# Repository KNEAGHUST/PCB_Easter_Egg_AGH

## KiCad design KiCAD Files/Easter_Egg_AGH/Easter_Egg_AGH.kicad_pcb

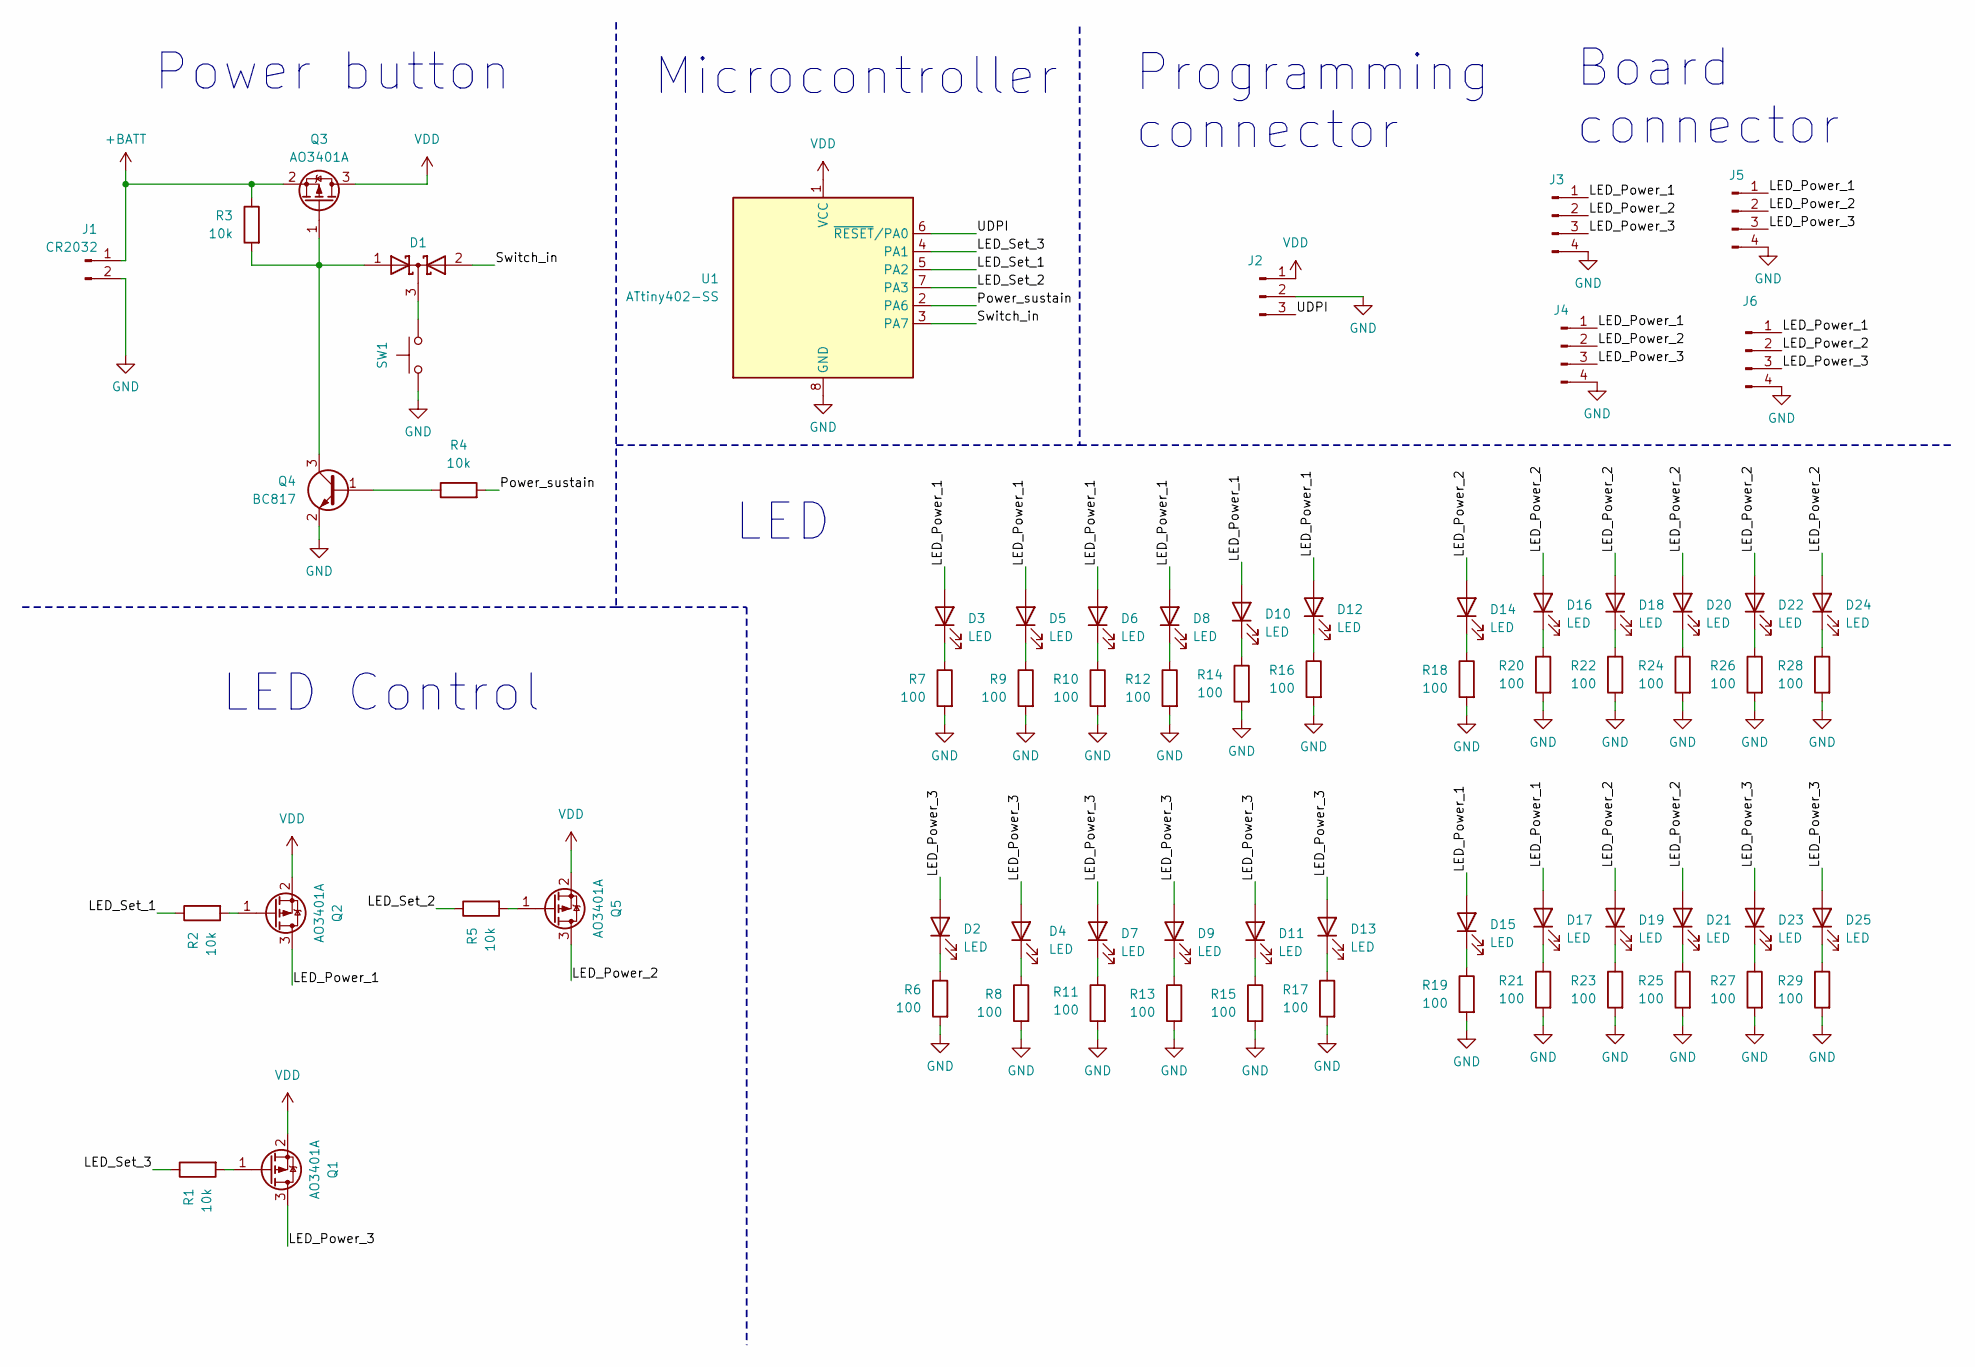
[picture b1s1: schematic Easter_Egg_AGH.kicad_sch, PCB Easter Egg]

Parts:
D1: D_Schottky_Dual_CommonCathode_AAK; SOT-23
D2, D3, D4, D5, D6, D7, D8, D9, D10, D11, D12, D13, D14, D15, D16, D17, D18, D19, D20, D21, D22, D23, D24, D25: LED; LED_0805_2012Metric_Pad1.15x1.40mm_HandSolder
J1: CR2032; BC-2002
J2: Conn_01x03_Pin; PinHeader_1x03_P2.54mm_Vertical
J3, J4, J5, J6: Conn_01x04_Pin; Multi_board_connector
Q1, Q2, Q3, Q5: AO3401A; SOT-323_SC-70
Q4: BC817; SOT-23
R1, R2, R3, R4, R5: 10k; R_0805_2012Metric_Pad1.20x1.40mm_HandSolder
R6, R7, R8, R9, R10, R11, R12, R13, R14, R15, R16, R17, R18, R19, R20, R21, R22, R23, R24, R25, R26, R27, R28, R29: 100; R_0805_2012Metric_Pad1.20x1.40mm_HandSolder
SW1: SW_Omron_B3FS; SW_Push_1P1T_NO_6x6mm_H9.5mm
U1: ATtiny402-SS; SOIC-8_3.9x4.9mm_P1.27mm

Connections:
+BATT: J1.1, Q3.2 (S), R3.1
/LED_Power_1: D3.2 (A), D5.2 (A), D6.2 (A), D8.2 (A), D10.2 (A), D12.2 (A), D15.2 (A), D17.2 (A), J3.1, J4.1, J5.1, J6.1, Q2.3 (D)
/LED_Power_2: D14.2 (A), D16.2 (A), D18.2 (A), D19.2 (A), D20.2 (A), D21.2 (A), D22.2 (A), D24.2 (A), J3.2, J4.2, J5.2, J6.2, Q5.3 (D)
/LED_Power_3: D2.2 (A), D4.2 (A), D7.2 (A), D9.2 (A), D11.2 (A), D13.2 (A), D23.2 (A), D25.2 (A), J3.3, J4.3, J5.3, J6.3, Q1.3 (D)
/LED_Set_1: R2.1, U1.5 (PA2)
/LED_Set_2: R5.1, U1.7 (PA3)
/LED_Set_3: R1.1, U1.4 (PA1)
/Power_sustain: R4.2, U1.2 (PA6)
/Switch_in: D1.2 (A), U1.3 (PA7)
/UDPI: J2.3, U1.6 (~RESET/PA0)
GND: J1.2, J2.2, J3.4, J4.4, J5.4, J6.4, Q4.2 (E), R6.2, R7.2, R8.2, R9.2, R10.2, R11.2, R12.2, R13.2, R14.2, R15.2, R16.2, R17.2, R18.2, R19.2, R20.2, R21.2, R22.2, R23.2, R24.2, R25.2, R26.2, R27.2, R28.2, R29.2, SW1.1, U1.8 (GND)
unnamed: D1.3 (K), SW1.2
unnamed: D2.1 (K), R6.1
unnamed: D3.1 (K), R7.1
unnamed: D4.1 (K), R8.1
unnamed: D5.1 (K), R9.1
unnamed: D6.1 (K), R10.1
unnamed: D7.1 (K), R11.1
unnamed: D8.1 (K), R12.1
unnamed: D9.1 (K), R13.1
unnamed: D10.1 (K), R14.1
unnamed: D11.1 (K), R15.1
unnamed: D12.1 (K), R16.1
unnamed: D13.1 (K), R17.1
unnamed: D14.1 (K), R18.1
unnamed: D15.1 (K), R19.1
unnamed: D16.1 (K), R20.1
unnamed: D17.1 (K), R21.1
unnamed: D18.1 (K), R22.1
unnamed: D19.1 (K), R23.1
unnamed: D20.1 (K), R24.1
unnamed: D21.1 (K), R25.1
unnamed: D22.1 (K), R26.1
unnamed: D23.1 (K), R27.1
unnamed: D24.1 (K), R28.1
unnamed: D25.1 (K), R29.1
unnamed: Q1.1 (G), R1.2
unnamed: Q2.1 (G), R2.2
unnamed: D1.1 (A), Q3.1 (G), Q4.3 (C), R3.2
unnamed: Q4.1 (B), R4.1
unnamed: Q5.1 (G), R5.2
VDD: J2.1, Q1.2 (S), Q2.2 (S), Q3.3 (D), Q5.2 (S), U1.1 (VCC)

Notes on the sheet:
LED
Board connector
LED Control
Power button
Microcontroller
Programming connector

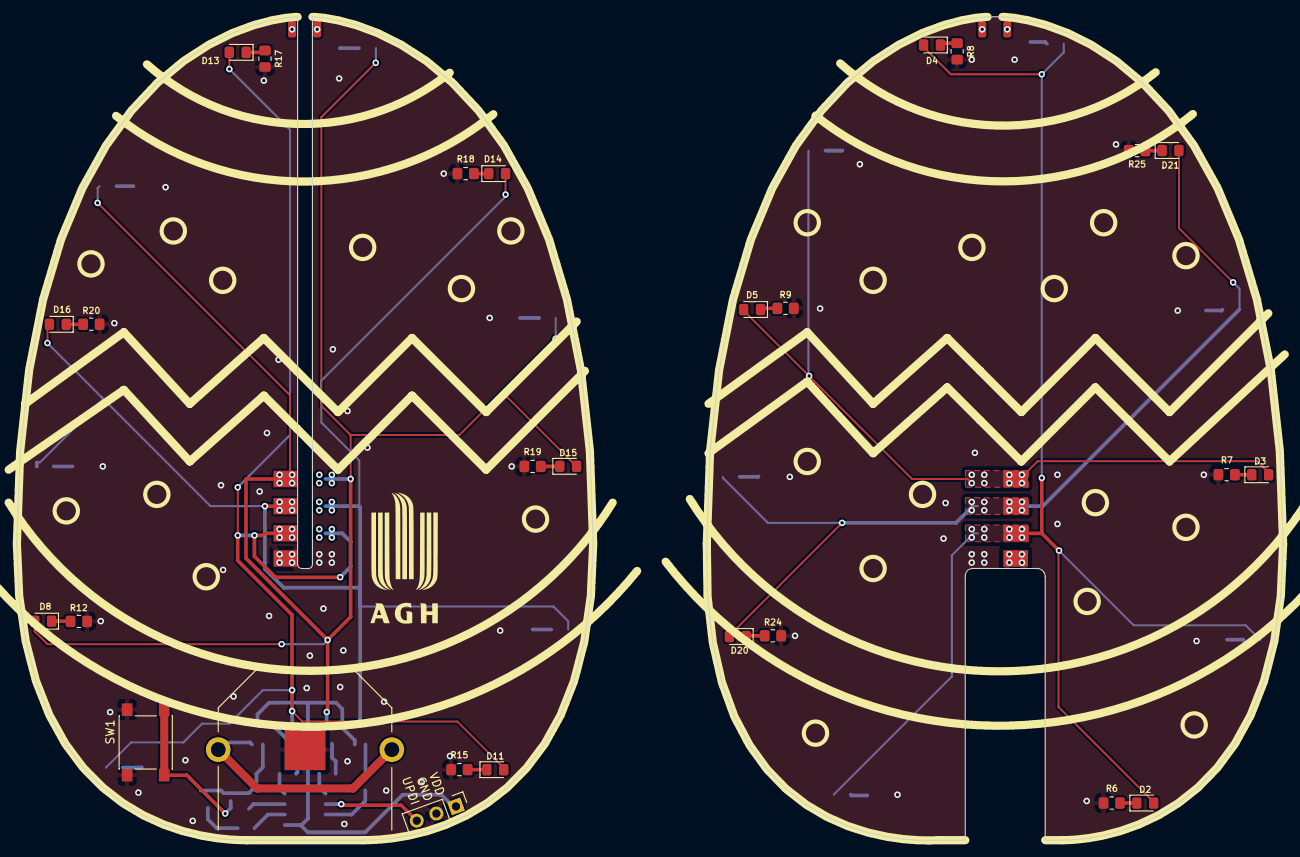
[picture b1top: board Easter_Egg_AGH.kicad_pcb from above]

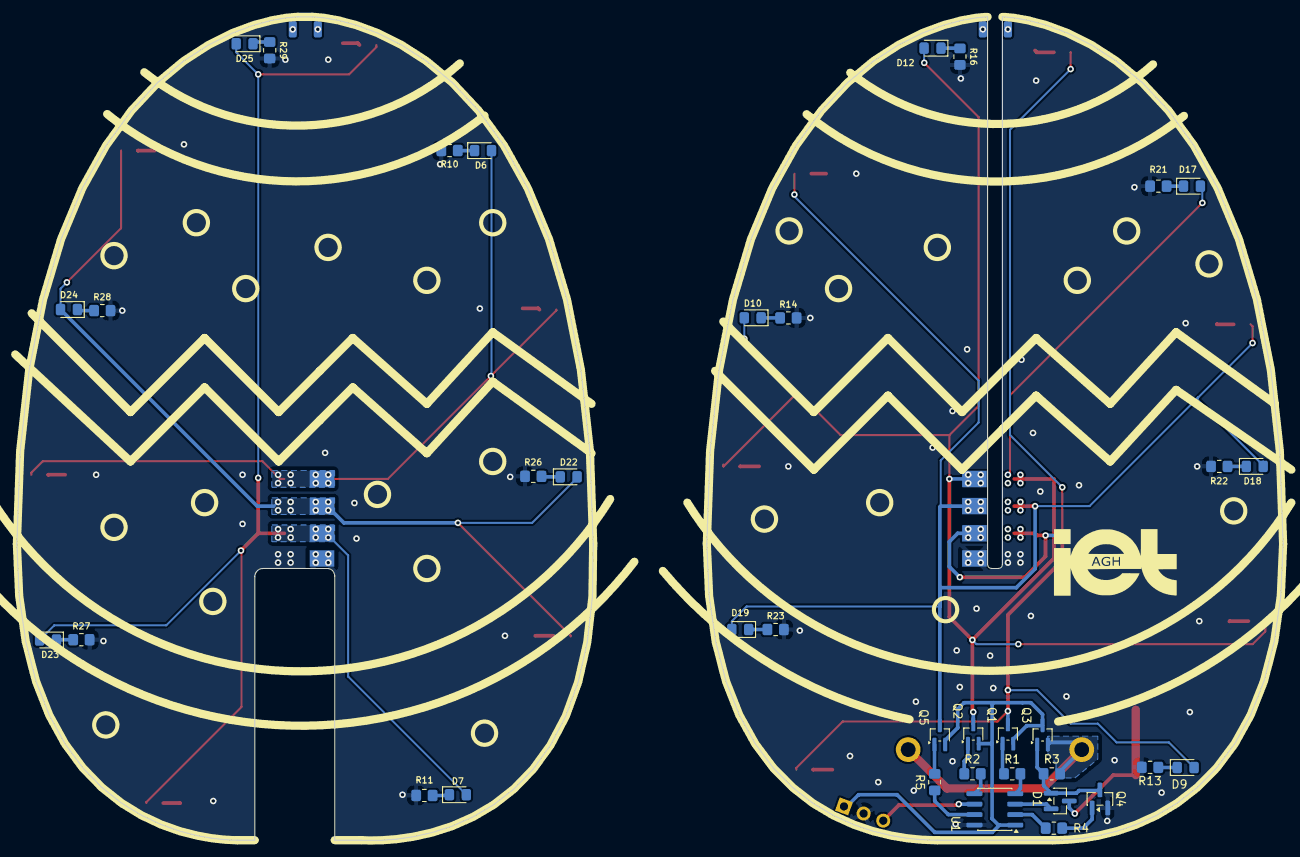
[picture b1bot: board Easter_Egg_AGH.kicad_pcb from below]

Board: 2 copper layers, 153.8 x 100.0 mm, 67 parts (38 on the bottom side), 42 nets.

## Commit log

2026-03-25 Added kicad files
